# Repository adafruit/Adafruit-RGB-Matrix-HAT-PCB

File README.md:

## Adafruit RGB Matrix HAT PCB

<a href="http://www.adafruit.com/products/1932"><br/>
Click here to purchase one from the Adafruit shop</a>

PCB files for the Adafruit RGB Matrix HAT. Format is EagleCAD schematic and board layout
* https://www.adafruit.com/product/2345

### DESCRIPTION
You can now create a dazzling display with your Raspberry Pi Model Zero/A+/B+/Pi 2 or Pi 3 with the Adafruit RGB Matrix HAT. This HAT plugs into your Pi and makes it super easy to control RGB matrices such as those we stock in the shop and create a colorful scrolling display or mini LED wall with ease.

This HAT is our finest to date, full of some really great circuitry. Let me break it down for you:

Simple design - plug in power, plug in IDC cable, run our Python code!
Power protection circuitry - you can plug a 5V 4A wall adapter into the HAT and it will automatically protect against negative, over or under-voltages! Yay for no accidental destruction of your setup.
Onboard level shifters to convert the RasPi's 3.3V to 5.0V logic for clean and glitch free matrix driving
DS1307 Real Time Clock can keep track of time for the Pi even when it is rebooted or powered down, to make for really nice time displays
Works with any of our 16x32, 32x32, 32x64 or 64x64 RGB LED Matrices with HUB75 connections. You can even chain multiple matrices together for a longer display, you can chain as many as you like but the bigger the display the harder it is on the Pi so keep that in mind! We don't recommend more than 64x128 pixel setups

As of October 2018, we now sell a version that can be used with 64x64 pixel matrices that have an 'E' address pin!

Please note: this HAT is only for use with HUB75 type RGB Matrices. Not for use with NeoPixel, DotStar, or other 'addressable' LEDs.

### License

Adafruit invests time and resources providing this open source design, please support Adafruit and open-source hardware by purchasing products from [Adafruit.com](https://www.adafruit.com)!

Creative Commons Attribution, Share-Alike license, check license.txt for more information All text above must be included in any redistribution - 
See license.txt for more information.

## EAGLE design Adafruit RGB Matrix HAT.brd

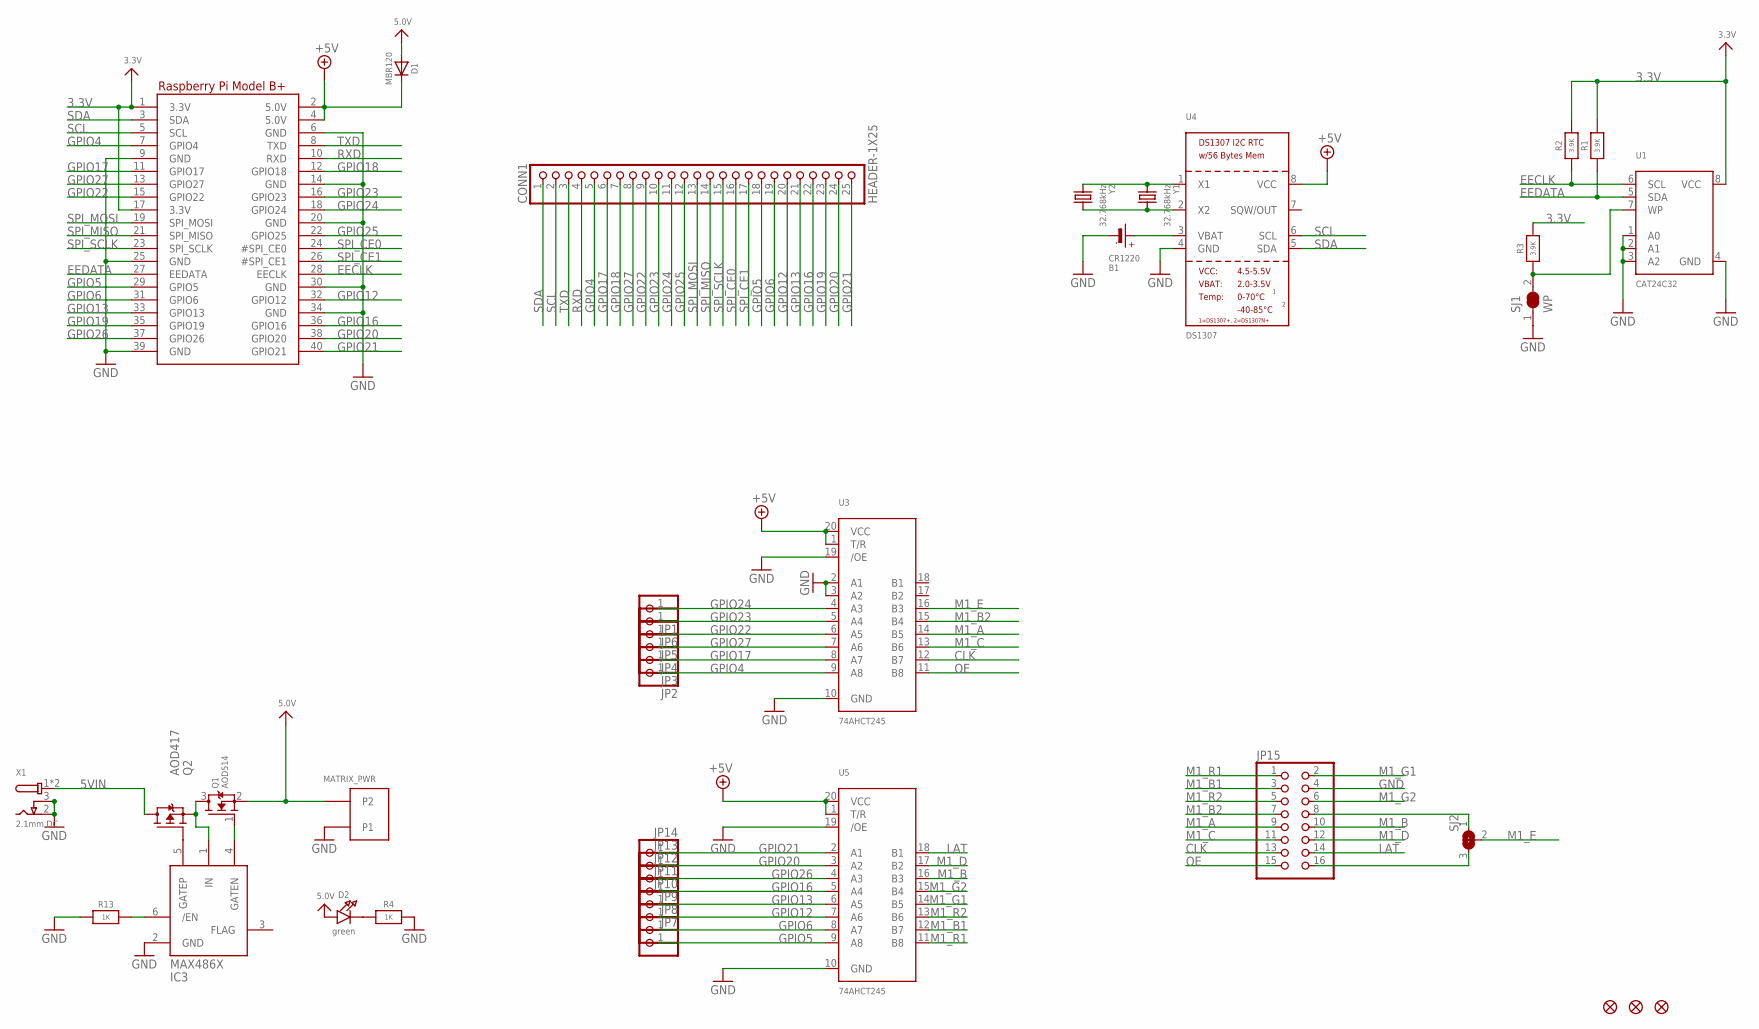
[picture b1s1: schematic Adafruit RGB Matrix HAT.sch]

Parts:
B1: CR1220
CONN1: HEADER-1X25; 1X25_ROUND_70MIL
D1: MBR120; SOD-123
D2: green; CHIPLED_0805_NOOUTLINE
FID1, FID2, FID3: FIDUCIAL_1MM
IC3: MAX4866T; SOT23-6
JP1, JP2, JP3, JP4, JP5, JP6, JP7, JP8, JP9, JP10, JP11, JP12, JP13, JP14: PINHD-1X1; 1X01
JP15: HEADER-2X8_SHROUDED; 2X08_SHROUDED
MATRIX_PWR: PINHEAD; TERMBLOCK508
Q1: AOD514; TO252
Q2: AOD417; TO252
R1, R2, R3: 3.9K; 0805-NO
R4, R13: 1K; 0805-NO
RPI1: RASPBERRYPI_BPLUS_HATSLOTS; PI_HAT_SLOTS
SJ1: WP; SOLDERJUMPER_CLOSEDWIRE
SJ2: SOLDERJUMPER_2WAY; SOLDERJUMPER_2WAY_OPEN_NOPASTE
U1: CAT24C32; SOIC8_150MIL
U3, U5: 74AHCT245; TSSOP20
U4: DS1307; SOIC8_150MIL
X1: 2.1mm DC; DCJACK_2MM_SMT
Y1: 32.768kHz; CRYSTAL_8X3.8
Y2: 32.768kHz; XTAL3215

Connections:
3.3V: R1.2, R2.2, R3.2, RPI1.1 (3.3V), RPI1.17 (3.3V), U1.8 (VCC)
5.0V: D1.A, D2.A, MATRIX_PWR.P$4 (P2), Q1.2 (S)
5VIN: Q2.3 (D), X1.1 (PWR), X1.1' (PWR)
+5V: D1.C, RPI1.2 (5.0V), RPI1.4 (5.0V), U3.1 (T/R), U3.20 (VCC), U4.8 (VCC), U5.1 (T/R), U5.20 (VCC)
CLK: JP15.13, U3.12 (B7)
EECLK: R2.1, RPI1.28 (EECLK), U1.6 (SCL)
EEDATA: R1.1, RPI1.27 (EEDATA), U1.5 (SDA)
GND: B1.-, IC3.2 (GND), JP15.4, MATRIX_PWR.P$3 (P1), R4.2, R13.1, RPI1.6 (GND), RPI1.9 (GND), RPI1.14 (GND), RPI1.20 (GND), RPI1.25 (GND), RPI1.30 (GND), RPI1.34 (GND), RPI1.39 (GND), SJ1.1, U1.1 (A0), U1.2 (A1), U1.3 (A2), U1.4 (GND), U3.2 (A1), U3.3 (A2), U3.10 (GND), U3.19 (/OE), U4.4 (GND), U5.10 (GND), U5.19 (/OE), X1.2 (GND), X1.3 (GNDBREAK)
GPIO4: CONN1.5, JP2.1, RPI1.7 (GPIO4), U3.9 (A8)
GPIO5: CONN1.18, JP7.1, RPI1.29 (GPIO5), U5.9 (A8)
GPIO6: CONN1.19, JP8.1, RPI1.31 (GPIO6), U5.8 (A7)
GPIO12: CONN1.20, JP9.1, RPI1.32 (GPIO12), U5.7 (A6)
GPIO13: CONN1.21, JP10.1, RPI1.33 (GPIO13), U5.6 (A5)
GPIO16: CONN1.22, JP11.1, RPI1.36 (GPIO16), U5.5 (A4)
GPIO17: CONN1.6, JP3.1, RPI1.11 (GPIO17), U3.8 (A7)
GPIO18: CONN1.7, RPI1.12 (GPIO18)
GPIO19: CONN1.23, RPI1.35 (GPIO19)
GPIO20: CONN1.24, JP13.1, RPI1.38 (GPIO20), U5.3 (A2)
GPIO21: CONN1.25, JP14.1, RPI1.40 (GPIO21), U5.2 (A1)
GPIO22: CONN1.9, JP5.1, RPI1.15 (GPIO22), U3.6 (A5)
GPIO23: CONN1.10, JP6.1, RPI1.16 (GPIO23), U3.5 (A4)
GPIO24: CONN1.11, JP1.1, RPI1.18 (GPIO24), U3.4 (A3)
GPIO25: CONN1.12, RPI1.22 (GPIO25)
GPIO26: JP12.1, RPI1.37 (GPIO26), U5.4 (A3)
GPIO27: CONN1.8, JP4.1, RPI1.13 (GPIO27), U3.7 (A6)
LAT: JP15.14, U5.18 (B1)
M1_A: JP15.9, U3.14 (B5)
M1_B: JP15.10, U5.16 (B3)
M1_B1: JP15.3, U5.12 (B7)
M1_B2: JP15.7, U3.15 (B4)
M1_C: JP15.11, U3.13 (B6)
M1_D: JP15.12, U5.17 (B2)
M1_E: SJ2.2, U3.16 (B3)
M1_E': JP15.8, SJ2.1
M1_E'': JP15.16, SJ2.3
M1_G1: JP15.2, U5.14 (B5)
M1_G2: JP15.6, U5.15 (B4)
M1_R1: JP15.1, U5.11 (B8)
M1_R2: JP15.5, U5.13 (B6)
unnamed: IC3.6 (/EN), R13.2
unnamed: U4.1 (X1), Y1.P$1 (1), Y2.P$1 (1)
unnamed: U4.2 (X2), Y1.P$4 (2), Y2.P$2 (2)
unnamed: D2.C, R4.1
unnamed: IC3.1 (IN), Q1.3 (D), Q2.2 (S)
unnamed: IC3.4 (GATEN), Q1.1 (G)
unnamed: IC3.5 (GATEP), Q2.1 (G)
unnamed: B1.+$1 (+), B1.+$2 (+), U4.3 (VBAT)
unnamed: R3.1, SJ1.2, U1.7 (WP)
OE: JP15.15, U3.11 (B8)
RXD: CONN1.4, RPI1.10 (RXD)
SCL: CONN1.2, RPI1.5 (SCL), U4.6 (SCL)
SDA: CONN1.1, RPI1.3 (SDA), U4.5 (SDA)
SPI_CE0: CONN1.16, RPI1.24 (#SPI_CE0)
SPI_CE1: CONN1.17, RPI1.26 (#SPI_CE1)
SPI_MISO: CONN1.14, RPI1.21 (SPI_MISO)
SPI_MOSI: CONN1.13, RPI1.19 (SPI_MOSI)
SPI_SCLK: CONN1.15, RPI1.23 (SPI_SCLK)
TXD: CONN1.3, RPI1.8 (TXD)

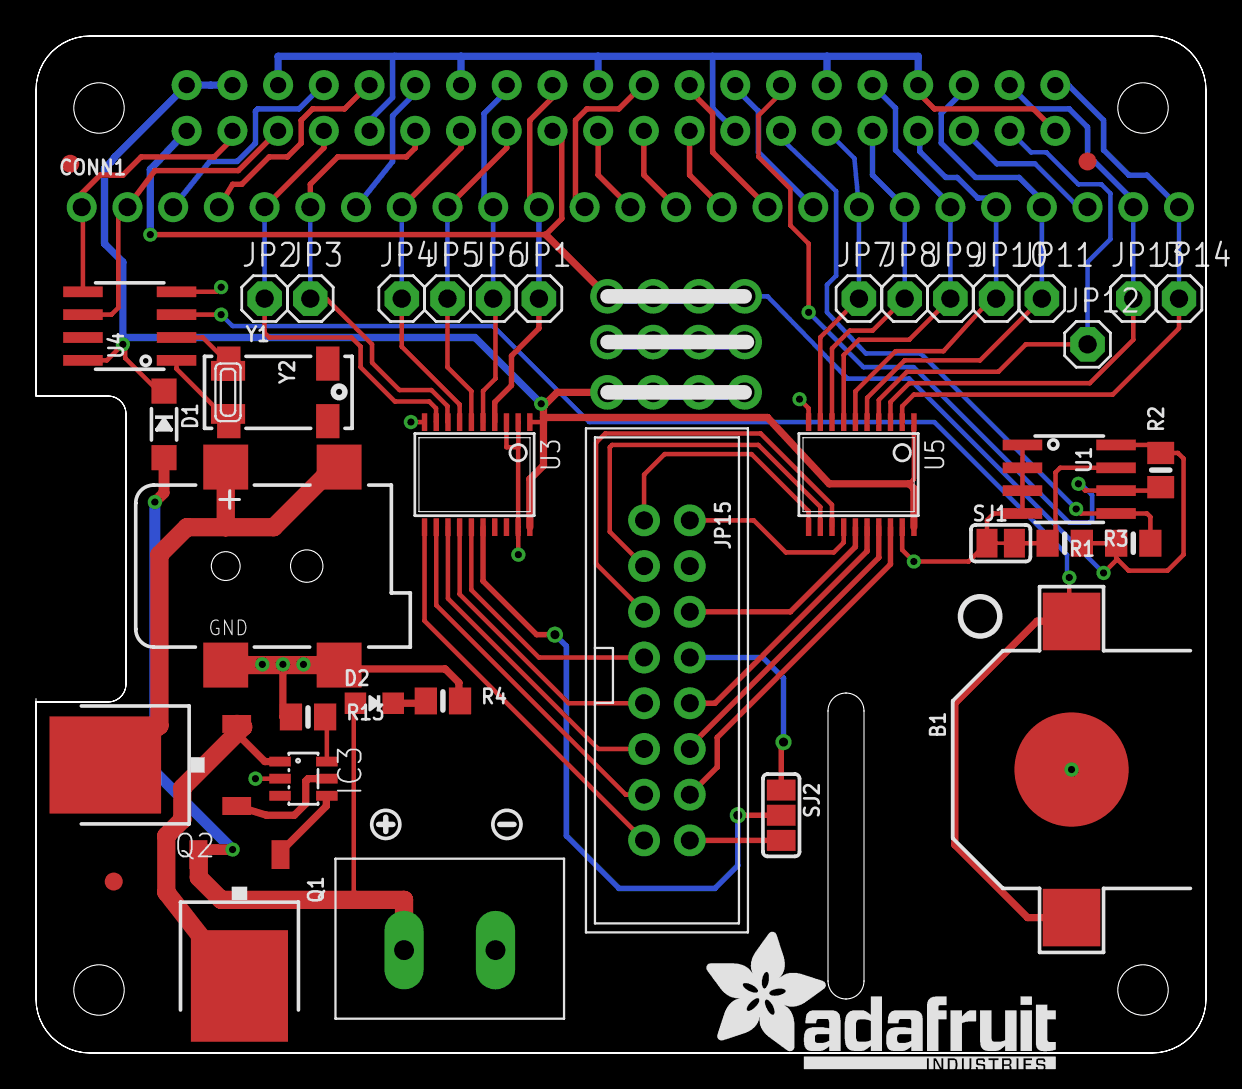
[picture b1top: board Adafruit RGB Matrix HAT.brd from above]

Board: 2 copper layers, 65.0 x 56.5 mm, 97 parts (0 on the bottom side), 58 nets.

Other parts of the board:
PLABEL0: PLABEL0
PLABEL1: PLABEL1
PLABEL2: PLABEL2
PLABEL3: PLABEL3
PLABEL4: PLABEL4
PLABEL5: PLABEL5
PLABEL6: PLABEL6
PLABEL7: PLABEL7
PLABEL8: PLABEL8
PLABEL9: PLABEL9
PLABEL10: PLABEL10
PLABEL11: PLABEL11
PLABEL12: PLABEL12
PLABEL13: PLABEL13
PLABEL14: PLABEL14
PLABEL15: PLABEL15
PLABEL16: PLABEL16
PLABEL17: PLABEL17
PLABEL18: PLABEL18
PLABEL19: PLABEL19
PLABEL20: PLABEL20
PLABEL21: PLABEL21
PLABEL22: PLABEL22
PLABEL23: PLABEL23
PLABEL24: PLABEL24
PLABEL25: PLABEL25
PLABEL26: PLABEL26
PLABEL27: PLABEL27
PLABEL28: PLABEL28
PLABEL29: PLABEL29
PLABEL30: PLABEL30
PLABEL31: PLABEL31
PLABEL32: PLABEL32
PLABEL33: PLABEL33
PLABEL34: PLABEL34
PLABEL35: PLABEL35
PLABEL36: PLABEL36
PLABEL37: PLABEL37
PLABEL38: PLABEL38
PLABEL39: PLABEL39
PLABEL40: PLABEL40
PLABEL41: PLABEL41
PLABEL42: PLABEL42
PLABEL43: PLABEL43
PLABEL44: PLABEL44
PLABEL45: PLABEL45
PLABEL46: PLABEL46
PLABEL47: PLABEL47
PLABEL48: PLABEL48
PLABEL49: PLABEL49
PLABEL50: PLABEL50
PLABEL51: PLABEL51
U$3: PCBFEAT-REV-056
U$10: SYMBOL_PLUS
U$11: SYMBOL_MINUS
U$12: ADAFRUIT_TEXT_20MM

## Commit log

2016-10-04 init
2024-04-03 Update to Rev C

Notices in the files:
parts and their libraries:
microbuilder: This work is placed in the public domain, and may be freely used for commercial and non-commercial work with the following conditions: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
